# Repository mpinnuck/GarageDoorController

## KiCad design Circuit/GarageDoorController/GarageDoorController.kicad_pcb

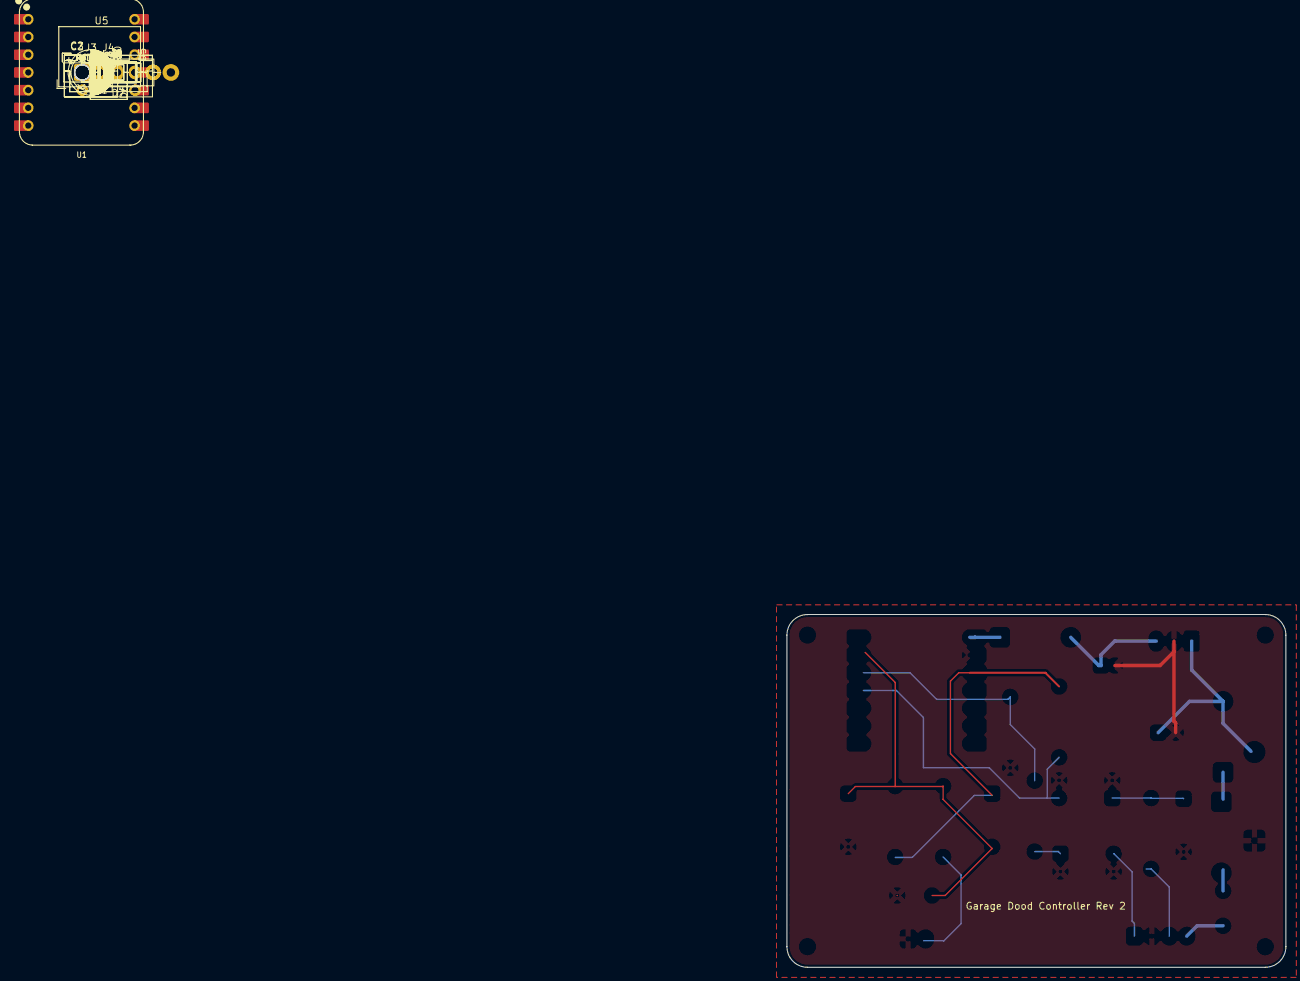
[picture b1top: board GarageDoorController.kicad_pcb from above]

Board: 2 copper layers, 71.5 x 50.6 mm, 23 parts (0 on the bottom side), 16 nets.

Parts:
C1: 100nF; C_Disc_D10.0mm_W2.5mm_P5.00mm
C2: 10uF 50V; CP_Radial_D6.3mm_P2.50mm
C3: 22uF 16V; CP_Radial_D5.0mm_P2.00mm
D2, D3, D4: 1N4148; D_DO-35_SOD27_P7.62mm_Horizontal
D5: 1N4007; D_DO-41_SOD81_P10.16mm_Horizontal
D6: P6KE30CA; D_DO-15_P12.70mm_Horizontal
D7: 1N5819; D_DO-41_SOD81_P10.16mm_Horizontal
D8: 1N4740A 10V 1W; D_DO-41_SOD81_P10.16mm_Horizontal
F1: MF-R020 0.2A; C_Disc_D5.0mm_W2.5mm_P5.00mm
J3: JST PH 2-pin; JST_XH_B2B-XH-A_1x02_P2.50mm_Vertical
J4: JST PH 4-pin; JST_XH_B4B-XH-A_1x04_P2.50mm_Vertical
R1, R9: 10k; R_Axial_DIN0207_L6.3mm_D2.5mm_P10.16mm_Horizontal
R6: 1k; R_Axial_DIN0207_L6.3mm_D2.5mm_P10.16mm_Horizontal
R7: 330R; R_Axial_DIN0207_L6.3mm_D2.5mm_P10.16mm_Horizontal
R8: 4k7 1/4W; R_Axial_DIN0207_L6.3mm_D2.5mm_P10.16mm_Horizontal
R10: 100k; R_Axial_DIN0207_L6.3mm_D2.5mm_P10.16mm_Horizontal
U1: XIAO-ESP32-C3-DIP; XIAO-ESP32C3-DIP
U3: TLP222A; DIP-4_W7.62mm
U4: PC817; DIP-4_W7.62mm
U5: R-78E5.0-0.5; Converter_DCDC_RECOM_R-78E-0.5_THT

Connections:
+3V3: D2.1 (K), R1.1, R9.1, U1.12 (VCC_3V3)
/Opener control/LAMP: J4.3, R8.2
/Opener control/OPENER_24V: F1.1, J4.4
/Opener control/PB: J4.1, U3.4
GND: C1.2, C2.2, C3.2, D3.2 (A), D4.2 (A), D6.1 (A1), J3.1, J4.2, R10.2, U1.13 (GND), U3.2, U3.3, U4.2, U4.3, U5.2 (GND)
unnamed: C1.1, D2.2 (A), D3.1 (K), R1.2, R6.2, U1.2 (GPIO3/A1/D1)
unnamed: D4.1 (K), R8.1, U4.1
unnamed: D5.2 (A), F1.2
unnamed: D5.1 (K), D8.1 (K)
unnamed: C2.1, D6.2 (A2), D8.2 (A), U5.1 (IN)
unnamed: C3.1, D7.2 (A), U5.3 (OUT)
unnamed: J3.2, R6.1
unnamed: R7.2, U3.1
OPENER_MOVING: R9.2, U1.4 (GPIO5/A3/D3), U4.4
OPENER_TRIG: R7.1, R10.1, U1.3 (GPIO4/A2/D2)
XIAO_5V: D7.1 (K), U1.14 (VBUS)
